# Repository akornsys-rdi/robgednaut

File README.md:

# Robgednaut #

Plataforma de introducción a la robótica, robusta y fácil de usar.

```
                                      'cdkKXWMMMWNXOxl,.
                                .,lkKWMMMMMMMMMMMMMMMMMMXOd:.
                            .;dKMMMMMMMMMMMMMMMMMMMMMMMMMMMMMNkc.
                          :OWMMMMMMMMMMMMMMMMMMMMMMMMMMMMMMMMMMMW0l.
                       .dNMMMMMMMMWKOxoc:;;,,;:cldkKWMMMMMMMMMMMMMMWk,
                     .kWMMMMMW0o;.                   .:o0WMMMMMMMMMMMM0,
                   .xMMMMMXd,                       .    .;kWMMMMMMMMMMMO.
                  :NMMMNd,                         xMW0.     :KMMMMMMMMMMNc
                 dMMMXl.                          .NMNo        ,KMMMMMMMMMMd
                kMMWl                            .KMW;           cNMMMMMMMMMk
               xMWx.                            .KMWc             .OMMMMMMMMMO
              lMW;                   .:c:.......OMMo                xMMMMMMMMMl
             'WN'                  :dc. .OMMMMMMMMW:                 xMMMMMMMMN.
             kW;                  .K      OMMMMMMMMMNc                KMMMMMMMMl
            .Wo                    kl      kMMMMMMMMMMOlkKNMKc        :MMMMMMMM0
            ,K                     X.       cNMMMMMMMMMMKxo0MMNd.      NMMMMMMMW
            ::                    .X         .kWMMMMMMMM'   .oXMMWk    kMMMMMMMM
            ,.            .;ccccld.X.          .oXMMMMMM,      oNK;    dMMMMMMMW
            .       .,cccc:.     O;O;             'oKMMK               xMMMMMMM0
                  'xc'.    .,cld00lo'                .lk.              0MMMMMMMl
                  ,0. .:cokKOdl:'.                     x:             .WMMMMMMN.
                   .d00xlccdo;          .c,..  .'c:..:d:              oMMMMMMMl
                 ;dc:'  .lclkOo,       'OlkOdc:;'..::.               .NMMMMMMO
                ..do.  c0kxxOloko,    .O0o..dl                      .KMMMMMMO
            'o0WMX'.ol..cokxlx0dxkl. .0Ol   k,                     .XMMMMMMk
        .:kNMWOl'    .dl  c:c:ldd0codOko   k:                     'XMMMMMWo
      :OWWOo'          .dl  ,ll:.lo:0kx   d:                     oWMMMMMX,
   'xWMMXl'.             .dc 'lol..Oxk   ol                    ,KMMMMMXc
 '0MMMMMMMMWO.             ,x;    kl0.  od                   ,0MMMMMKc
:WMMMMWWWMMMk               ':d;.k'.oc:ol                 .oXMMMMXd'
 ..... ,KMN;.,lOx      .   'Wo ,o.                    .,dXMMMMKo'
     ;0MMMWNMMMK.  .:kNd   K0:                   ..:d0WMMXOo;.
   :KMMMMMMMMMX. :OWMMM:  xW'            ..,;coxO0Okdl:'.
 cXMMMMMMWMMMM0OWMMMMMMk;0Ml
OMWXOo:'..NMMMMMMMMMMMMMMMx
..       kMMMMMMMMMNWMMMMk
        xMMMMMMMNd,kMMMWo
       dMMMMMWO:  .WMMN;
      ;MMMWOc.     d0c
      lMMk.
```

## Presentación ##

### _Robgednaut_ es creatividad. ###

El nombre está formado por un acrónimo de **Rob**otic (Robótica), Rug**ged** (endurecido) y _-**naut**_ (como astronauta). Es un nombre que define a la perfección lo que es e inspira esta plataforma. Pero no es un nombre muy amigable para ser pronunciado, por eso nosotros lo hemos abreviado cariñosamente en _Roben_, ¡tú puedes hacer lo mismo si quieres!

### _Robgednaut_ es educación libre. ###

Ha sido diseñado para cubrir la carencia de una plataforma educativa robótica que sea libre, asequible y fácil de usar. Desde su sencillez de uso esconde gran potencia y capacidad versátil, así como robustez y fiabilidad. Esto lo hace ideal para procesos de aprendizaje, proyectos, maquetas o productos finales.

### _Robgednaut_ es entretenimiento. ###

Desde la experiencia en entornos educativos, ha sido pensado para cubrir todas las necesidades habituales de éstos dentro del contexto de robótica pedagógica o de áreas STEM. Es sabido que romper cosas es parte normal del proceso de aprendizaje, por ello en la base de concepto de esta plataforma están incluídas múltiples protecciones contra los problemas y errores más habituales.

    *[STEM]: Science, technology, engineering y mathematics*

### _Robgednaut_ es flexibilidad. ###

Te permite hacer realidad tus ideas sin condicionarlas. Es extremadamente moldeable al carecer de electrónica de control y tener conexiones que pueden actuar como entradas o salida multipropósito. Es más, ha sido diseñado para ser usada en conjunción con Arduino, conocida marca que mantiene la filosofía de esta plataforma en cuanto a la orientación educativa y abierta.

### _Robgednaut_ es un universo. ###

Aporta una solución todo en uno, capaz de alimentar dispositivos externos y controlarlos, aparte de los integrados. Por medio de interfaces de comunicación puede ser controlado de forma remota desde un ordenador, dispositivos móviles o funcionar por sí mismo. Además, para integrarse con esta plataforma, están en desarrollo un montón de complementos que expanden las posibilidades mientras se mantienen las bases del proyecto original.

### _Robgednaut_ es lo que desees. ###

Está pensado para que te puedas sentir cómodo. Por ello es ideal para todas las edades. Permite diferentes entornos de programación para adecuarse a cada nivel educativo, y su forma de conexionado permite desde montajes rápidos a través de cocodrilos, o resistentes borneros de clema. Su sistema de alimentación permite funcionar tanto a partir de pilas como de adaptadores de corriente.

### _Robgednaut_ es Taller de Inventores. ###

Desarrollado desde la carencia observada en entornos educativos, se ha probado con éxito de forma piloto dentro del programa de [Taller de Inventores](http://tallerinventores.github.io/), siendo un elemento céntrico en el kit de materiales proporcionado por esta actividad y en los desarrollos realizados.

## Versiones ##

-   La primera versión de _Robgednaut_, conocida simplemente como _Roben_ fue una prueba de concepto y viabilidad. A pesar de que funcionaba con éxito, se observaron múltiples posibilidades de mejora, que deribaron en la siguiente versión.  
-   _Robgednaut Zond_, segunda versión y que debe su nombre al [programa Zond](https://es.wikipedia.org/wiki/Programa_Zond), expande y mejora la version previa en muchos aspectos, manteniendo la misma filosofia. Por desgracia, también introduce cambios que impiden la retrocompatibilidad del diseño. Aunque seguramente esto no te suponga ningún problema.

## Licencia ##

_Robgednaut_ es hardware y software libre liberado bajo [GNU/GPL](https://www.gnu.org/licenses/gpl.html). Más detalles en el archivo [README](https://github.com/akornsys-rdi/robgednaut/blob/master/README.md) del proyecto.

* * *

# _Robgednaut Roben_ #

_Robgednaut_ es la primera generación de esta plataforma. Esta implementación destaca por su sencillez de diseño, enfocado a su uso. Además es más eficiente que sus semejantes, al usar regulación conmutada.

Sus conexiones son los suficientemente amplias como para que puedan ser conectadas con cocodrilos, con un taladro que permite uniones con hilo conductor, y con la separación entre conexiones idónea para montar borneros de doscientas o trescientas milésimas de pulgada. Por supuesto en cualquier caso pueden ser soldadas.

La inclusión de un controlador de motores tipo puente en H, permite poder manejar los tipos de motores más normales, así como solenoides y otras cargas que demanden una corriente moderada. Este controlador se ha elegido pensando en su fácil sustitución en caso de dañarse.

## Diseño y esquemático ##

Los archivos fuente de diseño y los archivos de fabricación están disponibles en [GitHub](https://github.com/akornsys-rdi/robgednaut/tree/release-1/brd). La placa ha sido diseñada con [KiCad EDA](http://kicad-pcb.org/). Se puede acceder aquí directamente al [Esquemático ^PDF^](https://github.com/akornsys-rdi/robgednaut/raw/release-1/brd/bin/roben.pdf).

En el diseño de la placa, se ha tenido en cuenta los costes de fabricación, optimizando el diseño para reducirlos en la medida de lo posible (ancho de pistas vs espesor de cobre, diámetro de taladros y vías, número de capas y tamaño de la PCB).

## Características ##

Las características más relevantes de este diseño:

### Especificaciones ###

| Parámetro | Valor |
|------:|:-----|
| Microcontrolador | Ninguno, zócalo para Arduino Nano v3.x |
| Tensión de funcionamiento (lógica) | 5 V |
| Tensión de entrada (límites) | 6-28 V |
| Conexiones de entrada/salida | 4 |
| Conexiones de motores | 4 |
| Dimensiones | 47,625 x 90,17 mm (1.875 x 3.55 pulgadas) |

Para las especificaciones de Arduino Nano visite la [página oficial](https://www.arduino.cc/en/Main/ArduinoBoardNano).

### Protecciones ###

| Parámetro | Valor | Método |
|------:|:-----|:-----|
| Protección contra sobrecorriente en entrada de alimentación | 2 A | Fusible de restablecimiento (PPTC) |
| Protección contra inversión de polaridad de entrada de alimentación | -40 V | Diodo Schottky |
| Protección contra inyección de tensión en salida 5 V | 45 V | Diodo Schottky |
| Protección contra sobrecorriente en salida 5 V | 2 A | Controlador DC-DC |
| Protección contra sobrecorriente en entrada/salida | 23 mA | Resistencia |
| Protección contra tensión inadecuada en entrada/salida | -10 a 36 V | Diodo Zener |
| Protección contra sobrecorriente en salida de motores | 1 A | Apagado térmico del controlador |

### Alimentación ###

La alimentación se realiza a través de un bornero de alta calidad, con capacidad para conexión a través de cocodrilos. El rango de tensión funcional de esta entrada es de entre seis a veintiocho voltios. Debido a que son valores límite, es recomendable proporcionar una tensión segura dentro de este rango.

La conexión por USB de Arduino Nano tiene la capacidad de alimentar la plataforma, pero puede no proporcionar toda la corriente necesaria para su correcto funcionamiento. Asegúrate de usar siempre la alimentación principal si tienes circuitos montados y vas a conectar el USB.

> Advertencia: Alimentar _Robgednaut_ únicamente a través del puerto USB de Arduino puede provocar comportamientos anómalos y posibles daños al elemento que esté suministrando tensión al USB (normalmente un ordenador).

Las cuatro conexiones superiores de la placa son la salida de alimentación que ésta provee. La salida consiste en 5 V regulados con una capacidad total máxima de 2 A. Esta capacidad de corriente se ve reducida especialmente si se están usando motores al mismo tiempo.

    [^_image1]: 1. Borne positivo de entrada de alimentación. 2. Borne negativo de entrada de alimentación. 3. Conexión de salida positivo 5 V `+V`. 4. Conexión de salida negativo `GND`.

### Microcontrolador ###

_Robgednaut_ carece de microcontrolador, decisión que responde a los siguientes argumentos:

-   Proveer de un zócalo permite el fácil reemplazo o intercambio de microcontroladores a modo de módulos.  
-   Soporta múltiples entornos de desarrollo con el mismo esquema de conexiones.  
-   Aprovecha el ecosistema de Arduino y su comunidad (ver abajo).  
-   Permite la integración de desarrollos propios.  
-   Abarata la propia plataforma.

El zócalo aporta compatibilidad directa con Arduino Nano v3.x, como primera opción para el módulo microcontrolador. Arduino posee un IDE desarollado estable con múltiples IDE alternativos y un gran conjunto de librerías. Como plataforma es maduro y estable, con una gran comunidad a su alrededor, por lo que se crea una relación simbiótica. Además, el microcontrolador es electricamente robusto y usa compilador libre.

> Nota: El zócalo estandarizado compatible es de 32 patillas. Debido a que Arduino Nano posee 30 patillas, se usa como referencia el pin uno para su alineación.

En el zócalo del microcontrolador es posible colocar, con un adaptador, múltiples entornos embebidos. ¡Usa _Robgednaut_ con tu PIC, MSP430, ARM, 8051 o la que sea tu plataforma habitual!

    [^_image2]: Detalle de orientación y alineación de montaje de Arduino Nano sobre _Robgednaut_.

### Entrada/Salida ###

Las cuatro conexiones de entrada/salida de propósito general provistas por _Robgednaut_ agrupan muchas de las funciones específicas de Arduino, concentrando todo su potencial en pocas conexiones. De esta manera, es más sencillo entender y manejar. Si echas en falta conexiones, siempre puedes expandir mediante las conexiones serie digitales o dar el salto usar el módulo microcontrolador por sí solo.

> Advertencia: Asegúrate de tener el firmare adecuado antes de conectar tu Arduino Nano a _Robgednaut_. De no ser así, puedes dañar tu Arduino.

Todas las conexiones de _Robgednaut_ son entradas analógicas y entradas/salidas digitales, pero además poseen algunas capacidades especiales:

-   Interrupciones externas en las conexiones `A` y `B`.  
-   Salidas PWM en las conexiones `B` y `D`.  
-   Bus [SPI](https://es.wikipedia.org/wiki/Serial_Peripheral_Interface) en `C` (SCK) y `D` (MOSI)[^1^].  
-   Bus [I^2^C](https://es.wikipedia.org/wiki/I%C2%B2C) en `C` (SCL) y `D` (SDA).

    [^1^]: MISO no presente. SS puede ser cualquiera de las otras conexiones.

| Robgednaut | Arduino Nano v3.x | Función |
|-----:|:-----|:-----|
| `A` | `D2`, `A2` | Entrada analógica, entrada/salida digital, interrupción externa |
| `B` | `D3`, `A3` | Entrada analógica, entrada/salida digital, salida PWM, interrupción externa |
| `C` | `D13`, `A5` | Entrada analógica, entrada/salida digital, Comunicación serie (SCL y SCK) |
| `D` | `D11`, `A4` | Entrada analógica, entrada/salida digital, salida PWM, Comunicación serie (SDA y MOSI) |

    [^_image3]: 1. Conexión `A`. 2. Conexión `B`. 3. Conexión `C`. 4. Conexión `D`.

### Motores ###

La plataforma integra un controlador de motores tipo puente en H, capaz de mover hasta cuatro motores de continua en un único sentido, dos en ambos sentidos, o un motor paso a paso. Además, el controlador puede ser usado además para mover otro tipo de cargas de corriente media, como pueden ser solenoides, lámparas o ser usadas como salidas digitales convencionales[^2^].

    [^2^]: Las salidas del controlador de motores son tipo _push-pull_, lo que puede ocasionar problemas con aquellos dispositivos que requieran alta impedancia o temporizaciones precisas.

El controlador usado está montado en zócalo para su fácil reemplazo en caso de dañarse. Originalmente se integra el componente SN754410, que es una versión mejorada del L293D, pero compatible con ésta. Cualquiera de los dos controladores puede usarse en _Robgednaut_.

Este controlador integra dos puentes en H, dividido en mitades. Cada puente en H debe ser habilitado para su uso.

| Robgednaut | Arduino Nano v3.x | Función |
|-----:|:-----|:-----|
| 1+ | `D7` (en), `D5` (PWM) | Salida de la mitad positiva del puente en H 1[^3^] |
| 1- | `D7` (en), `D6` (PWM) | Salida de la mitad negativa del puente en H 1[^3^] |
| 2+ | `D8` (en), `D9` (PWM) | Salida de la mitad positiva del puente en H 2[^3^] |
| 2- | `D8` (en), `D10` (PWM) | Salida de la mitad negativa del puente en H 2[^3^] |

    [^3^]: Las polaridades del las mitades de los puente en H se pueden invertir por software. Usando estas conexiones por defecto los motores de continua avanzarán hacia delante.

    [^_image4]: 1. Borne positivo de conexión `1+`. 2. Borne negativo de conexión `1-`. 3. Borne positivo de conexión `2+`. 4. Borne negativo de conexión `2-`.

## Programación ##

La programación depende directamente de qué microcontrolador/entorno se esté usando. Puede programarse desde el IDE del entorno embebido, o usarse programación por bloques con un interfaz adecuado. Esto es: Programar _Robgednaut_ con Arduino en Scratch usando Firmata.

### Firmware ###

Por defecto, _Robgednaut_ provee una librería para el IDE de Arduino, así como un firmware específico para Arduino compatible con Firmata. Ambos pueden encontrarse en el repositorio de firmware de [Github](https://github.com/akornsys-rdi/robgednaut-firmware).

> Advertencia: Si creas tu propio firmware sin usar la librería proporcionada, recuerda al usar las conexiones de entrada/salida poner en alta impedancia la conexión que no estés usando en cada momento, o podrás dañar tu Arduino.

## Caja ##

Para la protección de _Robgednaut_, así como para evitar posibles cortocircuitos durante su uso, se incluye una caja imprimible en 3D para resguardar la plataforma. Esta caja incluye la serigrafía de las conexiones y facilita su montaje.

Puede accederse a los archivos fuente de diseño y los archivos de fabricación en [GitHub](https://github.com/akornsys-rdi/robgednaut/tree/release-1/3d).

* * *

# _Robgednaut Zond_ #

_Robgednaut Zond_ es la segunda generación de esta plataforma. Esta implementación es una revisión exhaustiva de la anterior, que incluye gran cantidad de mejoras y cambios. ¡Practicamente se ha duplicado el número de componentes en placa!

Se mantienen las características conexiones amplias, así como el controlador de motores y el zócalo para el microcontrolador.

> Advertencia: Algunos de los cambios de _Robgednaut Zond_, la hacen incompatible en firmware y conexionado con respecto a la anterior versión. Comprueba las tablas de conexionado para adaptar tu sistema.

## Novedades ##

-   _Robgednaut_ ahora integra los dipositivos más comunes para que no tengas que conectarlos. Se trata de tres indicadores LED de diferentes colores, dos pulsadores y un altavoz piezoeléctrico.  
-   Todo es mejor con LED. Ahora, cada una de las conexiones lleva un LED para indicar su estado, sin que ello afecte a su funcionamiento.  
-   Rango de tensión de entrada ampliado. Ahora es posible hacer funcionar _Robgednaut_ desde tres voltios hasta treinta y dos. Además, la alimentación de entrada puede conectarse a través de un bornero o mediante conector de barril.  
-   Aviso de batería baja, puesto que la plataforma está pensada para ser móvil, se ha añadido un indicador que se activa cuando la tensión de entrada baja de los cuatro voltios.  
-   Interruptor de encendido, para no tener que desconectar la alimentación.  
-   Puedes elegir la tensión a la que se activan los motores (o lo que conectes en estas salidas). Ahora se puede elegir entre la tensión de entrada o cinco voltios.  
-   Comunicación bluetooth, para poder controlar tu _Robgednaut_ desde dispositivos inteligentes.

## Diseño y esquemático ##

Los archivos fuente de diseño y los archivos de fabricación están disponibles en [GitHub](https://github.com/akornsys-rdi/robgednaut/tree/release-2/brd). La placa ha sido diseñada con [KiCad EDA](http://kicad-pcb.org/). Se puede acceder aquí directamente al [Esquemático ^PDF^](https://github.com/akornsys-rdi/robgednaut/raw/release-2/brd/bin/roben.pdf).

En el diseño de la placa, se ha tenido en cuenta los costes de fabricación, optimizando el diseño para reducirlos en la medida de lo posible (ancho de pistas vs espesor de cobre, diámetro de taladros y vías, número de capas y tamaño de la PCB).

Así mismo, se ha cuidado la elección de los componentes usados para que no suponga un gran aumento de costes por todos los cambios en comparación de la versión previa.

## Características ##

Las características más relevantes de este diseño:

### Especificaciones ###

| Parámetro | Valor |
|------:|:-----|
| Microcontrolador | Ninguno, zócalo para Arduino Nano v3.x |
| Tensión de funcionamiento (lógica) | 5 V |
| Tensión de entrada (límites) | 3-32 V |
| Conexiones de entrada/salida | 4 |
| Conexiones de motores | 4 |
| Dimensiones | 47,625 x 90,17 mm (1.875 x 3.55 pulgadas) |

Para las especificaciones de Arduino Nano visite la [página oficial](https://www.arduino.cc/en/Main/ArduinoBoardNano).

### Protecciones ###

| Parámetro | Valor | Método |
|------:|:-----|:-----|
| Protección contra sobrecorriente en entrada de alimentación | 1.5 A | Fusible de restablecimiento (PPTC) |
| Protección contra inversión de polaridad de entrada de alimentación | -40 V | Diodo Schottky |
| Protección contra inyección de tensión en salida 5 V | 45 V | Diodo Schottky |
| Protección contra sobrecorriente en salida 5 V | 2 A | Controlador DC-DC |
| Protección contra sobrecorriente en entrada/salida | 23 mA | Resistencia |
| Protección contra tensión inadecuada en entrada/salida | -10 a 36 V | Diodo Zener |
| Protección contra sobrecorriente en salida de motores | 1 A | Apagado térmico del controlador |

### Alimentación ###

La alimentación se realiza a través de una de las dos opciones posibles: Un bornero de alta calidad, con capacidad para conexión a través de cocodrilos, o un conector tipo barril. El conector hembra de la opción seleccionada se suelda sobre la placa. El rango de tensión funcional de esta entrada es de entre tres a treinta y dos voltios. Debido a que son valores límite, es recomendable proporcionar una tensión segura dentro de este rango.

Ser móvil ha sido uno de los objetivos de esta plataforma desde el principio, por ello se ha rediseñado el regulador para funcionar mejor a través de pilas. Pero las pilas progresivamente se descargan y todo el sistema pierde fuerza. Así que en esta revisión se ha añadido también un indicador de batería baja, que se activa cuando la tensión de entrada baja de los cuatro voltios. Esto lo hace ideal para cuando se alimenta a partir de paquetes de cuatro baterías o tres pilas.

La mayoría de los entornos de desarrollo obligan a desconectar el cable para apagar el sistema, algo que casi se da por hecho. Pero ya está solucionado, se ha añadido un interruptor que apaga el regulador, para que no tengas que desmontar nada.

La conexión por USB de Arduino Nano tiene la capacidad de alimentar la plataforma independientemente del interruptor de apagado, pero puede no proporcionar toda la corriente necesaria para su correcto funcionamiento. Asegúrate de usar siempre la alimentación principal si tienes circuitos montados y vas a conectar el USB.

> Advertencia: Alimentar _Robgednaut_ únicamente a través del puerto USB de Arduino puede provocar comportamientos anómalos y posibles daños al elemento que esté suministrando tensión al USB (normalmente un ordenador).

Las cuatro conexiones superiores de la placa son la salida de alimentación que ésta provee. La salida consiste en 5 V regulados con una capacidad total máxima de 2 A. Esta capacidad de corriente se ve reducida especialmente si se están usando motores al mismo tiempo.

    [^_image5]: 1. Borne positivo de entrada de alimentación. 2. Borne negativo de entrada de alimentación. 3. Conexión de salida positivo 5 V `+V`. 4. Conexión de salida negativo `GND`.

### Microcontrolador ###

_Robgednaut_ carece de microcontrolador, decisión que responde a los siguientes argumentos:

-   Proveer de un zócalo permite el fácil reemplazo o intercambio de microcontroladores a modo de módulos.  
-   Soporta múltiples entornos de desarrollo con el mismo esquema de conexiones.  
-   Aprovecha el ecosistema de Arduino y su comunidad (ver abajo).  
-   Permite la integración de desarrollos propios.  
-   Abarata la propia plataforma.

El zócalo aporta compatibilidad directa con Arduino Nano v3.x, como primera opción para el módulo microcontrolador. Arduino posee un IDE desarollado estable con múltiples IDE alternativos y un gran conjunto de librerías. Como plataforma es maduro y estable, con una gran comunidad a su alrededor, por lo que se crea una relación simbiótica. Además, el microcontrolador es electricamente robusto y usa compilador libre.

> Nota: El zócalo estandarizado compatible es de 32 patillas. Debido a que Arduino Nano posee 30 patillas, se usa como referencia el pin uno para su alineación.

En el zócalo del microcontrolador es posible colocar, con un adaptador, múltiples entornos embebidos. ¡Usa _Robgednaut_ con tu PIC, MSP430, ARM, 8051 o la que sea tu plataforma habitual!

    [^_image6]: Detalle de orientación y alineación de montaje de Arduino Nano sobre _Robgednaut_.

### Entrada/Salida ###

Las cuatro conexiones de entrada/salida de propósito general provistas por _Robgednaut_ agrupan muchas de las funciones específicas de Arduino, concentrando todo su potencial en pocas conexiones. De esta manera, es más sencillo entender y manejar. Si echas en falta conexiones, siempre puedes expandir mediante las conexiones serie digitales o dar el salto usar el módulo microcontrolador por sí solo.

> Advertencia: Asegúrate de tener el firmare adecuado antes de conectar tu Arduino Nano a _Robgednaut_. De no ser así, puedes dañar tu Arduino.

Todas las conexiones de _Robgednaut_ son entradas analógicas y entradas/salidas digitales, pero además poseen algunas capacidades especiales:

-   Interrupciones externas en las conexiones `A` y `B`.  
-   Salidas PWM en las conexiones `B` y `D`.  
-   Bus [SPI](https://es.wikipedia.org/wiki/Serial_Peripheral_Interface) en `C` (SCK) y `D` (MOSI)[^1^].  
-   Bus [I^2^C](https://es.wikipedia.org/wiki/I%C2%B2C) en `C` (SDA) y `D` (SCL).

    [^1^]: MISO no presente. SS puede ser cualquiera de las otras conexiones.

| Robgednaut | Arduino Nano v3.x | Función |
|-----:|:-----|:-----|
| `A` | `D2`, `A7` | Entrada analógica, entrada/salida digital, interrupción externa |
| `B` | `D3`, `A6` | Entrada analógica, entrada/salida digital, salida PWM, interrupción externa |
| `C` | `D13`, `A4` | Entrada analógica, entrada/salida digital, comunicación serie (SDA y SCK) |
| `D` | `D11`, `A5` | Entrada analógica, entrada/salida digital, salida PWM, comunicación serie (SCL y MOSI) |
| Interno | `D4` | Altavoz piezoeléctrico |
| Interno | `D12` | LED rojo |
| Interno | `A0` | LED amarillo |
| Interno | `A1` | LED verde |
| Interno | `A2` | Pulsador |
| Interno | `A3` | Pulsador |

    [^_image7]: 1. Conexión `A`. 2. Conexión `B`. 3. Conexión `C`. 4. Conexión `D`.

### Motores ###

La plataforma integra un controlador de motores tipo puente en H, capaz de mover hasta cuatro motores de continua en un único sentido, dos en ambos sentidos, o un motor paso a paso. Además, el controlador puede ser usado además para mover otro tipo de cargas de corriente media, como pueden ser solenoides, lámparas o ser usadas como salidas digitales convencionales[^2^].

    [^2^]: Las salidas del controlador de motores son tipo _push-pull_, lo que puede ocasionar problemas con aquellos dispositivos que requieran alta impedancia o temporizaciones precisas.

El controlador usado está montado en zócalo para su fácil reemplazo en caso de dañarse. Originalmente se integra el componente SN754410, que es una versión mejorada del L293D, pero compatible con ésta. Cualquiera de los dos controladores puede usarse en _Robgednaut_.

Este controlador integra dos puentes en H, dividido en mitades. Cada puente en H debe ser habilitado para su uso.

| Robgednaut | Arduino Nano v3.x | Función |
|-----:|:-----|:-----|
| 1+ | `D8` (en), `D10` (PWM) | Salida de la mitad positiva del puente en H 1[^3^] |
| 1- | `D7` (en), `D5` (PWM) | Salida de la mitad negativa del puente en H 1[^3^] |
| 2+ | `D8` (en), `D9` (PWM) | Salida de la mitad positiva del puente en H 2[^3^] |
| 2- | `D7` (en), `D6` (PWM) | Salida de la mitad negativa del puente en H 2[^3^] |

    [^3^]: Las polaridades del las mitades de los puente en H se pueden invertir por software. Usando estas conexiones por defecto los motores de continua avanzarán hacia delante.

    [^_image8]: 1. Borne positivo de conexión `1+`. 2. Borne negativo de conexión `1-`. 3. Borne positivo de conexión `2+`. 4. Borne negativo de conexión `2-`.

## Programación ##

La programación depende directamente de qué microcontrolador/entorno se esté usando. Puede programarse desde el IDE del entorno embebido, o usarse programación por bloques con un interfaz adecuado. Esto es: Programar _Robgednaut_ con Arduino en Scratch usando Firmata.

### Firmware ###

Por defecto, _Robgednaut_ provee una librería para el IDE de Arduino, así como un firmware específico para Arduino compatible con Firmata. Ambos pueden encontrarse en el repositorio de firmware de [Github](https://github.com/akornsys-rdi/robgednaut-firmware).

> Advertencia: Si creas tu propio firmware sin usar la librería proporcionada, recuerda al usar las conexiones de entrada/salida poner en alta impedancia la conexión que no estés usando en cada momento, o podrás dañar tu Arduino.

## Caja ##

Para la protección de _Robgednaut_, así como para evitar posibles cortocircuitos durante su uso, se incluye una caja imprimible en 3D para resguardar la plataforma. Esta caja incluye la serigrafía de las conexiones y facilita su montaje, mientras mantiene accesibles los componentes interactuables.

Puede accederse a los archivos fuente de diseño y los archivos de fabricación en [GitHub](https://github.com/akornsys-rdi/robgednaut/tree/release-2/3d).

* * *

Copyright (C) 2015-2016 kwendenarmo. This file is part of Robgednaut

Robgednaut is free software; you can redistribute it and/or modify it under the terms of the GNU General Public License as published by the Free Software Foundation; either version 3 of the License, or (at your option) any later version.

Robgednaut is distributed in the hope that it will be useful, but WITHOUT ANY WARRANTY; without even the implied warranty of MERCHANTABILITY or FITNESS FOR A PARTICULAR PURPOSE. See the GNU General Public License for more details

You should have received a copy of the GNU General Public License along with this program. If not, see <http://www.gnu.org/licenses/>.

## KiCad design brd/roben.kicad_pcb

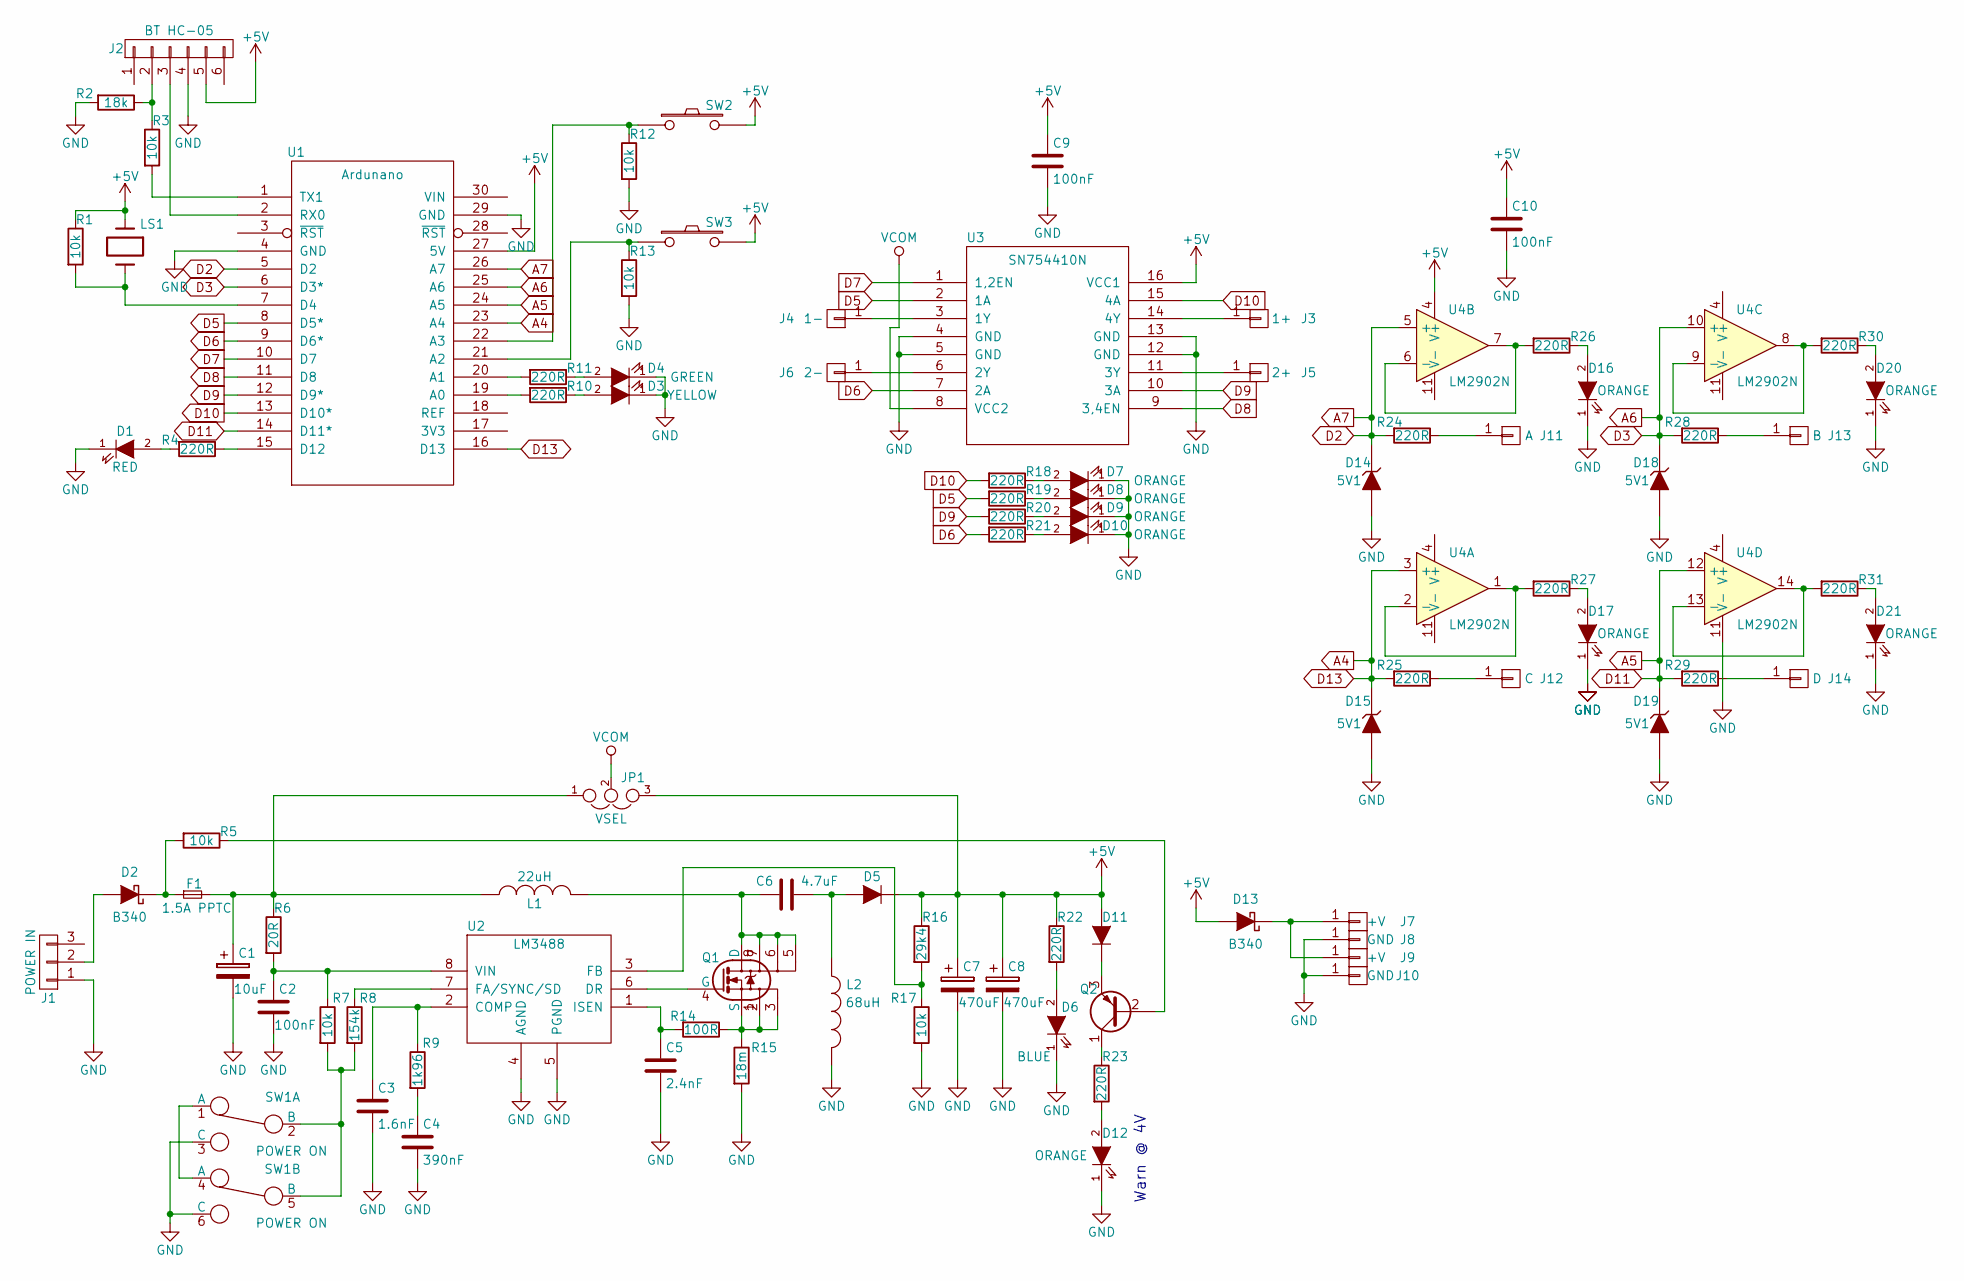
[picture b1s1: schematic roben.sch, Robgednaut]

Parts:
C1: 10uF; c_elec_5x5.3
C2, C9, C10: 100nF; C_0805_HandSoldering
C3: 1.6nF; C_0805_HandSoldering
C4: 390nF; C_0805_HandSoldering
C5: 2.4nF; C_0805_HandSoldering
C6: 4.7uF; C_1206_HandSoldering
C7, C8: 470uF; c_elec_8x10
D1: RED; LED-0805
D2, D13: B340; Diode-SMC_Handsoldering
D3: YELLOW; LED-0805
D4: GREEN; LED-0805
D5: SD2114S040S8R0; Diode-SMB_Handsoldering
D6: BLUE; LED-0805
D7, D8, D9, D10, D12, D16, D17, D20, D21: ORANGE; LED-0805
D11: TCMBD914; SOT-23_Handsoldering
D14, D15, D18, D19: 5V1; SOD-123
F1: 1.5A PPTC; Fuse_SMD2920
J1: POWER IN; combo-barrel5.5x2.1-2p5.08
J2: BT HC-05; HC-05
J3: 1+; SolderWirePad_single_2-5mmDrill
J4: 1-; SolderWirePad_single_2-5mmDrill
J5: 2+; SolderWirePad_single_2-5mmDrill
J6: 2-; SolderWirePad_single_2-5mmDrill
J7, J9: +V; SolderWirePad_single_2-5mmDrill
J8, J10: GND; SolderWirePad_single_2-5mmDrill
J11: A; SolderWirePad_single_2-5mmDrill
J12: C; SolderWirePad_single_2-5mmDrill
J13: B; SolderWirePad_single_2-5mmDrill
J14: D; SolderWirePad_single_2-5mmDrill
JP1: VSEL; M20-87703xx
L1: 22uH; coil-12x12h10
L2: 68uH; coil-13x13H7
LS1: AT-1224-TWT-5V-2-R
Q1: BUK7Y98; SOT-669_LFPAK_ThermalVias-1
Q2: BC856; SOT-23_Handsoldering
R1, R3, R5, R7, R12, R13, R17: 10k; R_0805_HandSoldering
R2: 18k; R_0805_HandSoldering
R4, R10, R11, R18, R19, R20, R21, R22, R23, R24, R25, R26, R27, R28, R29, R30, R31: 220R; R_0805_HandSoldering
R6: 20R; R_0805_HandSoldering
R8: 154k; R_0805_HandSoldering
R9: 1k96; R_0805_HandSoldering
R14: 100R; R_0805_HandSoldering
R15: 18m; 0612
R16: 29k4; R_0805_HandSoldering
SW1: POWER ON; JS202011SCQN
SW2, SW3: SW_PUSH; FSMxxJxH
U1: Ardunano
U2: LM3488; TSSOP-8_3x3mm_Pitch0.65mm
U3: SN754410N; DIP-16__300_ELL
U4: LM2902N; SOIC-14_3.9x8.7mm_Pitch1.27mm

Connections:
+5V: C7.1, C8.1, C9.1, C10.1, D5.1 (K), D11.1 (A), D13.2 (A), J2.5, JP1.3, LS1.1, R1.1, R16.1, R22.1, SW2.2, SW3.2, U1.27 (5V), U3.16 (VCC1), U4.4 (V+)
A4: D15.1 (K), R25.2, U1.16 (D13), U1.23 (A4), U4.3 (+)
A5: D19.1 (K), R29.2, U1.14 (D11*), U1.24 (A5), U4.12 (+)
A6: D18.1 (K), R28.2, U1.6 (D3*), U1.25 (A6), U4.10 (+)
A7: D14.1 (K), R24.2, U1.5 (D2), U1.26 (A7), U4.5 (+)
D5: R19.2, U1.8 (D5*), U3.2 (1A)
D6: R21.2, U1.9 (D6*), U3.7 (2A)
D7: U1.10 (D7), U3.1 (1,2EN)
D8: U1.11 (D8), U3.9 (3,4EN)
D9: R20.2, U1.12 (D9*), U3.10 (3A)
D10: R18.2, U1.13 (D10*), U3.15 (4A)
GND: C1.2, C2.2, C3.2, C4.2, C5.2, C7.2, C8.2, C9.2, C10.2, D1.1 (K), D3.1 (K), D4.1 (K), D6.1 (K), D7.1 (K), D8.1 (K), D9.1 (K), D10.1 (K), D12.1 (K), D14.2 (A), D15.2 (A), D16.1 (K), D17.1 (K), D18.2 (A), D19.2 (A), D20.1 (K), D21.1 (K), J1.1, J2.4, J8.1, J10.1, L2.2, R2.2, R12.2, R13.2, R15.2, R17.2, SW1.3 (C), SW1.6 (C), U1.4 (GND), U1.29 (GND), U2.4 (AGND), U2.5 (PGND), U3.4 (GND), U3.5 (GND), U3.12 (GND), U3.13 (GND), U4.11 (V-)
unnamed: C1.1, F1.2, JP1.1, L1.1, R6.1
unnamed: C2.1, R6.2, R7.1, U2.8 (VIN)
unnamed: C3.1, R9.1, U2.2 (COMP)
unnamed: C4.1, R9.2
unnamed: C5.1, R14.2, U2.1 (ISEN)
unnamed: C6.1, D5.2 (A), L2.1
unnamed: C6.2, L1.2, Q1.5, Q1.6, Q1.7, Q1.8 (D)
unnamed: D1.2 (A), R4.2
unnamed: D2.1 (K), F1.1, R5.2
unnamed: D2.2 (A), J1.2
unnamed: D3.2 (A), R10.1
unnamed: D4.2 (A), R11.1
unnamed: D6.2 (A), R22.2
unnamed: D7.2 (A), R18.1
unnamed: D8.2 (A), R19.1
unnamed: D9.2 (A), R20.1
unnamed: D10.2 (A), R21.1
unnamed: D11.3 (K), Q2.3 (E)
unnamed: D12.2 (A), R23.2
unnamed: D13.1 (K), J7.1, J9.1
unnamed: D16.2 (A), R26.1
unnamed: D17.2 (A), R27.1
unnamed: D20.2 (A), R30.1
unnamed: D21.2 (A), R31.1
unnamed: J2.2, R2.1, R3.1
unnamed: J2.3, U1.2 (RX0)
unnamed: J3.1, U3.14 (4Y)
unnamed: J4.1, U3.3 (1Y)
unnamed: J5.1, U3.11 (3Y)
unnamed: J6.1, U3.6 (2Y)
unnamed: J11.1, R24.1
unnamed 43: J12.1, R25.1; also elsewhere on the board
unnamed 44: J13.1, R28.1; also elsewhere on the board
unnamed 45: J14.1, R29.1; also elsewhere on the board
unnamed: LS1.2, R1.2, U1.7 (D4)
unnamed: Q1.1 (S), Q1.2, Q1.3, R14.1, R15.1
unnamed: Q1.4 (G), U2.6 (DR)
unnamed: Q2.1 (C), R23.1
unnamed: Q2.2 (B), R5.1
unnamed: R3.2, U1.1 (TX1)
unnamed: R4.1, U1.15 (D12)
unnamed: R7.2, R8.2, SW1.2 (B), SW1.5 (B)
unnamed: R8.1, U2.7 (FA/SYNC/SD)
unnamed: R10.2, U1.19 (A0)
unnamed: R11.2, U1.20 (A1)
unnamed: R12.1, SW2.1, U1.22 (A3)
unnamed: R13.1, SW3.1, U1.21 (A2)
unnamed: R16.2, R17.1, U2.3 (FB)
unnamed: R26.2, U4.6 (-), U4.7
unnamed: R27.2, U4.1, U4.2 (-)
unnamed: R30.2, U4.8, U4.9 (-)
unnamed: R31.2, U4.13 (-), U4.14
unnamed: SW1.1 (A), SW1.4 (A)
VCOM: JP1.2, U3.8 (VCC2)

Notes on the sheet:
Warn @ 4V

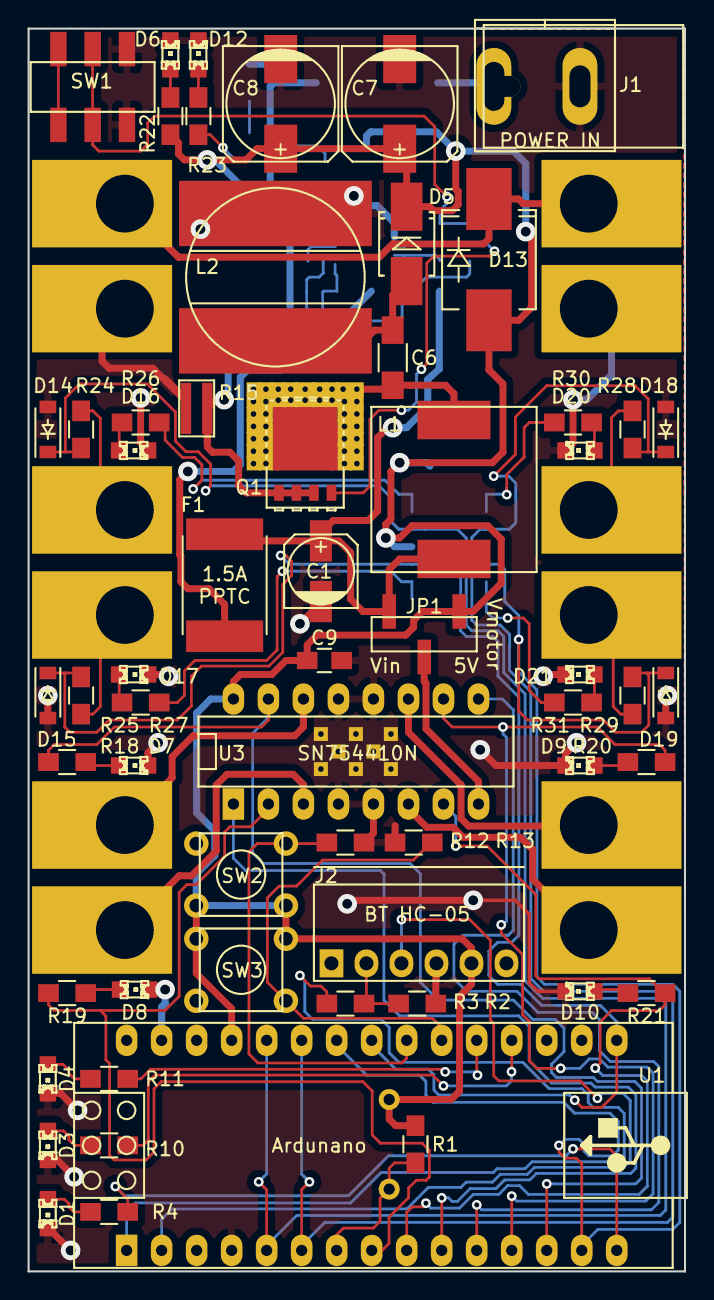
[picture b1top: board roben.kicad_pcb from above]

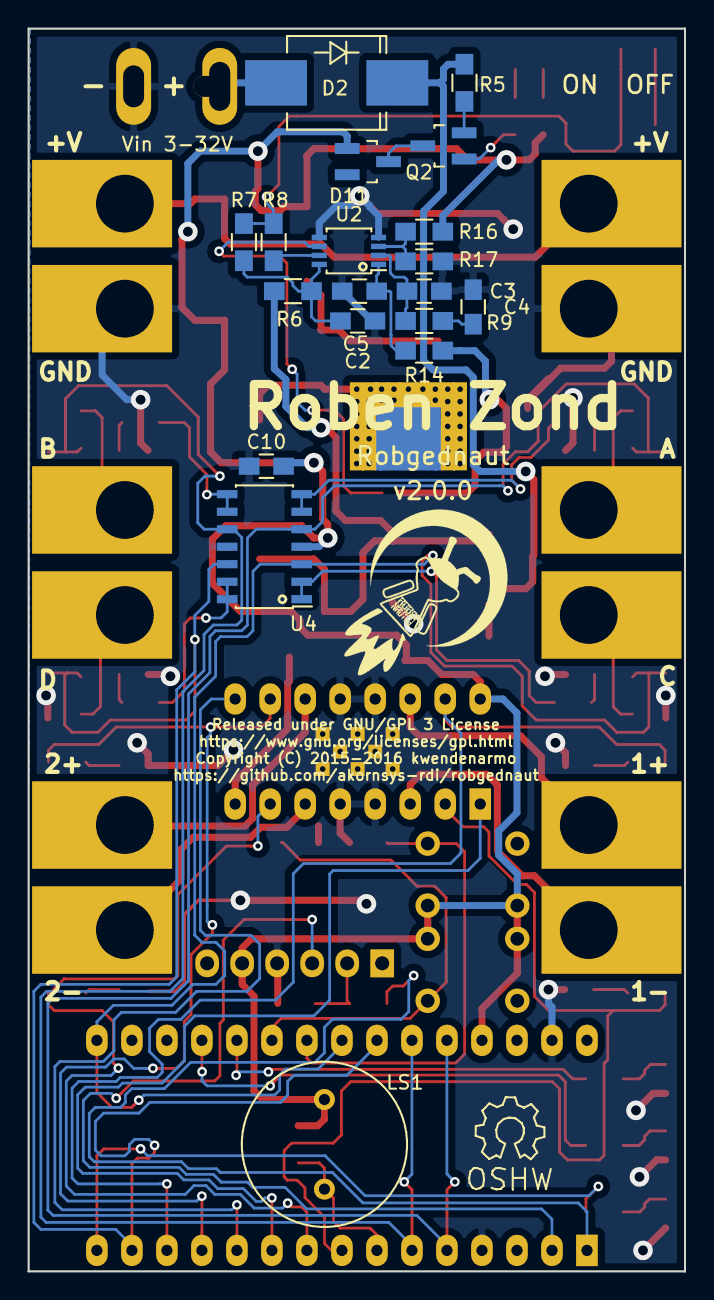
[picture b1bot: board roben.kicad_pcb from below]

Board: 2 copper layers, 47.6 x 90.2 mm, 91 parts (20 on the bottom side), 66 nets.

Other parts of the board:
B: B; SolderWirePad_single_2-5mmDrill
C: C; SolderWirePad_single_2-5mmDrill
D: D; SolderWirePad_single_2-5mmDrill
G1: LOGO; roben

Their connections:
unnamed 43: C.1; also elsewhere on the board
unnamed 44: B.1; also elsewhere on the board
unnamed 45: D.1; also elsewhere on the board

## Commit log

2015-09-10 new: doc: Subidos conjunto de archivos README
2015-09-10 new: dev: subida PCB
2015-09-10 chg: dev: añadidas referencias datasheet y BOM
2015-12-06 chg: dev: subido codigo demo !wip
2016-01-17 new: movido src a ``robgednaut-firmware`` repo
2016-01-17 new: importado ``robgednaut-firmware``
2016-01-17 chg::doc: actualizados archivos README
2016-01-17 new: modificada inversión de polaridad según #1
2016-01-18 new: reemplazado step-down por sepic, segun #2
2016-01-18 new: añadidos periféricos en pines libres, segun #4
2016-01-18 new: añadido interruptor de encendido, segun #6
2016-01-18 new: añadido indicador de bateria baja, segun #7
2016-01-23 chg: optimizado esquemático y circuito
2016-01-23 chg: añadido seleccion de tension para motores
2016-01-23 chg: añadidos indicadores de salida en motores
2016-01-23 chg: añadida comunicacion bluetooth
2016-01-23 chg: anotados componentes en esquematico
2016-01-23 chg: actualizada informacion de esquematico
2016-01-23 chg: creada netlist y asociaciones
2016-01-23 chg: finalizado esquematico
2016-01-31 chg: corregida conexion bluetooth
2016-01-31 chg: reanotados componentes
2016-01-31 chg: mejoradas asociaciones de zócalos, resuelto #3
2016-01-31 chg: BREAKING desplazadas conexiones analogicas
2016-01-31 chg: BREAKING intercambiadas salidas de motores
2016-01-31 chg: reordenados LED de motores en consonancia
2016-01-31 chg: BREAKING reasignadas uniones I/O
2016-01-31 chg: reordenadas salidas LED
2016-02-02 chg: generado pdf de esquematico
2016-02-02 chg: diseñado pcb
2016-02-02 chg: corregidos errores
2016-02-02 chg: generados archivos gerbers
2016-02-03 chg: añadidos BOM
2016-02-03 chg: añadido logo robgednaut
2016-02-03 chg: modificados archivos README
2016-02-03 chg: editados README
2016-02-15 Create gh-pages branch via GitHub
2016-02-29 new: editada web
2016-02-29 new: añadido README

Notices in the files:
README.md:
Copyright (C) 2015-2016 kwendenarmo. This file is part of Robgednaut
Robgednaut is free software; you can redistribute it and/or modify it under the terms of the GNU General Public License as published by the Free Software Foundation; either version 3 of the License, or (at your option) any later version.
brd/roben.kicad_pcb:
Released under GNU/GPL 3 License https://www.gnu.org/licenses/gpl.html
